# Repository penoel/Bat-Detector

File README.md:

# Bat-Detector
The bat detector takes ultrasonic sound from a source (bat, transmitter, etc) and adds it to a local oscillator.  The combined signal has a beat frequency (intermediate frequency) that is then filter to remove the higher frequencies.  It is currently used with a transmitter to show doppler shift.  The transmitter is mounted on a pendulum that swings towards and away from the detector.
## R7 should be 1.5k&#937; not ~~47k&#937;~~, R9 should be 560 &#937; not ~~1k&#937;~~, and lastly R11 should be 1k&#937; not ~~4.7k&#937;~~
These values work a lot better with this op amp (other values were better for the first one I used)

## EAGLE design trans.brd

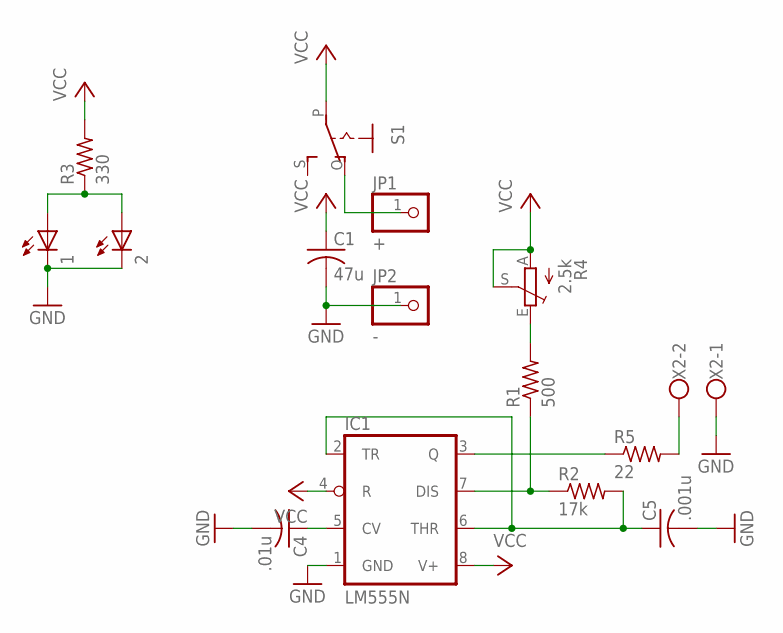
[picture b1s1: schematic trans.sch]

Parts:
1, 2: LED3MM
C1: 47u; C050-025X075
C4: .01u; C025-025X050
C5: .001u; C025-025X050
IC1: LM555N; DIL08
JP1: +; 1X01
JP2: -; 1X01
R1: 500; 0207/10
R2: 17k; 0207/10
R3: 330; 0207/10
R4: 2.5k; CA9V
R5: 22; 0207/10
S1: EG1218S; EG1218
X2: W237-102

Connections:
GND: 1.K (C), 2.K (C), C1.2, C4.2, C5.2, IC1.1 (GND), JP2.1, X2.1
unnamed: 1.A, 2.A, R3.1
unnamed: C4.1, IC1.5 (CV)
unnamed: C5.1, IC1.2 (TR), IC1.6 (THR), R2.2
unnamed: IC1.7 (DIS), R1.1, R2.1
unnamed: R1.2, R4.E
unnamed: IC1.3 (Q), R5.1
unnamed: JP1.1, S1.O
unnamed: R5.2, X2.2
VCC: C1.1, IC1.4 (R), IC1.8 (V+), R3.2, R4.A, R4.S, S1.P

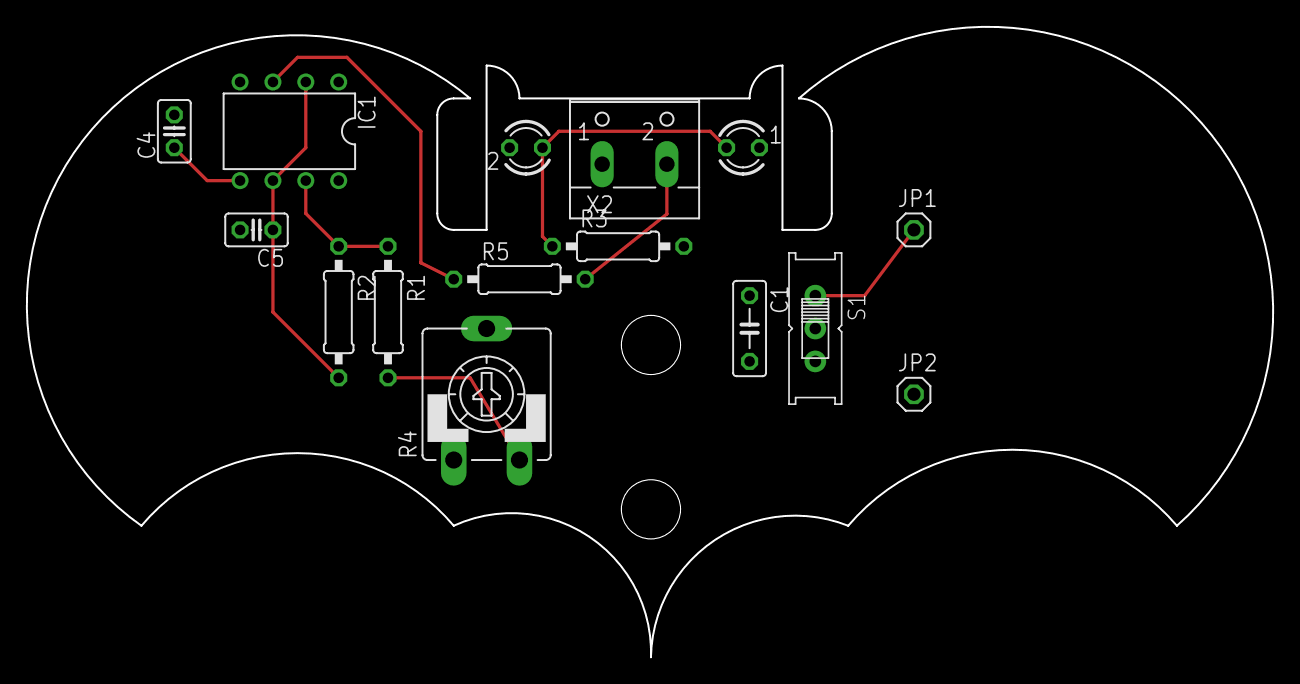
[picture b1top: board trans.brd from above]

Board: 2 copper layers, 96.3 x 48.7 mm, 15 parts (0 on the bottom side), 10 nets.

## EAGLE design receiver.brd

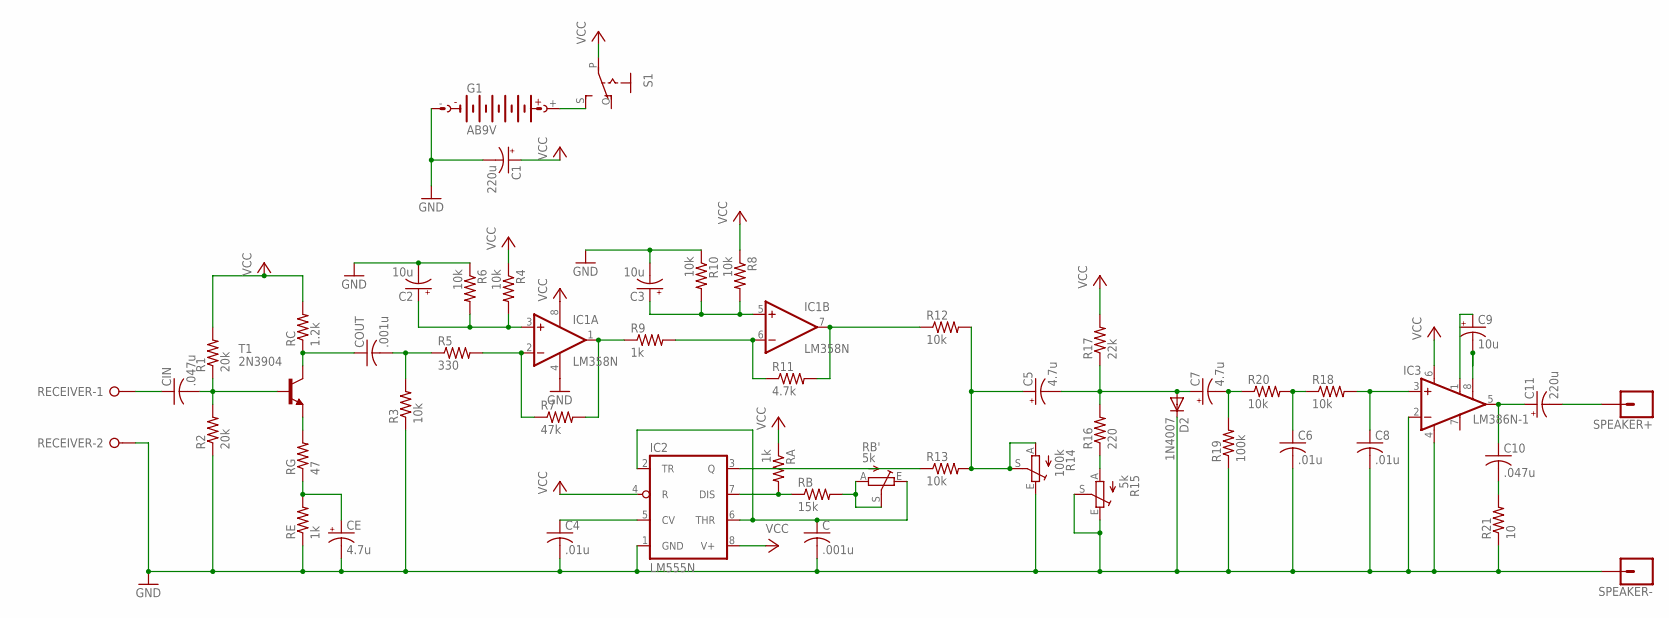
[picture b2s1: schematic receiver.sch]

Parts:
C: .001u; C050-024X044
C1, C11: 220u; B45181B
C2, C3, C9: 10u; B45181B
C4, C6, C8: .01u; C050-024X044
C5, C7: 4.7u; B45181B
C10: .047u; C050-024X044
CE: 4.7u; B45181B
CIN: .047u; C050-024X044
COUT: .001u; C050-024X044
D2: 1N4007; DO41-10
G1: AB9V
IC1: LM358N; DIL08
IC2: LM555N; DIL08-ROUND
IC3: LM386N-1; DIL08
R1, R2: 20k; 0207/10
R3, R4, R6, R8, R10, R12, R13, R18, R20: 10k; 0207/10
R5: 330; 0207/10
R7: 47k; 0207/10
R9: 1k; 0207/10
R11: 4.7k; 0207/10
R14: 100k; B25P
R15: 5k; B25P
R16: 220; 0207/10
R17: 22k; 0207/10
R19: 100k; 0207/10
R21: 10; 0207/10
RA: 1k; 0207/10
RB: 15k; 0207/10
RB': 5k; B25P
RC: 1.2k; 0207/10
RE: 1k; 0207/10
RECEIVER: W237-02P; W237-132
RG: 47; 0207/10
S1: EG1218S; EG1218
SPEAKER+: CONN_01; 1X01
SPEAKER-: CONN_01; 1X01
T1: 2N3904; TO92

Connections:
GND: C.2, C1.-, C2.-, C3.-, C4.2, C6.2, C8.2, CE.-, D2.C, G1.-, IC1.4 (V-), IC2.1 (GND), IC3.2 (-IN), IC3.4 (GND), R2.1, R3.1, R6.1, R10.1, R14.E, R15.E, R15.S, R19.1, R21.1, RE.1, RECEIVER.2, SPEAKER-.1
unnamed: CIN.1, RECEIVER.1
unnamed: CIN.2, R1.1, R2.2, T1.2 (B)
unnamed: COUT.2, R3.2, R5.1
unnamed: COUT.1, RC.1, T1.1 (C)
unnamed: RG.2, T1.3 (E)
unnamed: CE.+, RE.2, RG.1
unnamed: IC1.2 (-IN), R5.2, R7.1
unnamed: C2.+, IC1.3 (+IN), R4.2, R6.2
unnamed: C4.1, IC2.5 (CV)
unnamed: IC1.1 (OUT), R7.2, R9.1
unnamed: IC1.6 (-IN), R9.2, R11.1
unnamed: C.1, IC2.2 (TR), IC2.6 (THR), RB'.E
unnamed: IC1.7 (OUT), R11.2, R12.1
unnamed: C3.+, IC1.5 (+IN), R8.2, R10.2
unnamed: IC2.7 (DIS), RA.2, RB.1
unnamed: RB.2, RB'.A, RB'.S
unnamed: IC2.3 (Q), R13.1
unnamed: C5.+, R12.2, R13.2, R14.A, R14.S
unnamed: R15.A, R16.1
unnamed: C5.-, C7.+, D2.A, R16.2, R17.1
unnamed: C11.-, SPEAKER+.1
unnamed: C7.-, R19.2, R20.1
unnamed: C6.1, R18.1, R20.2
unnamed: C8.1, IC3.3 (+IN), R18.2
unnamed: C9.-, IC3.8 (GAIN)
unnamed: C9.+, IC3.1 (GAIN)
unnamed: C10.1, C11.+, IC3.5 (OUT)
unnamed: C10.2, R21.2
unnamed: G1.+, S1.S
VCC: C1.+, IC1.8 (V+), IC2.4 (R), IC2.8 (V+), IC3.6 (VS), R1.2, R4.1, R8.1, R17.2, RA.1, RC.2, S1.P

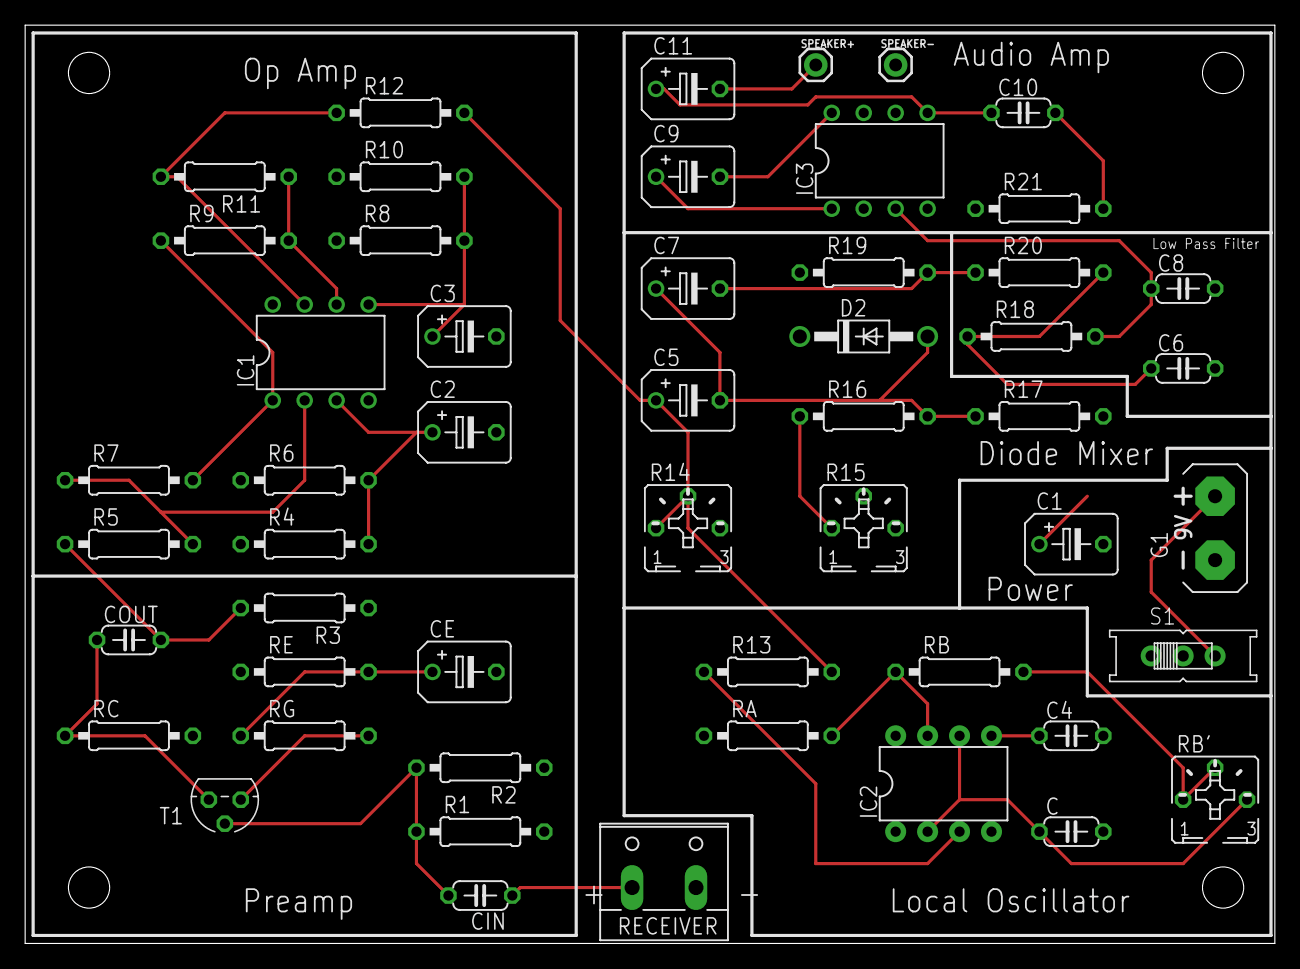
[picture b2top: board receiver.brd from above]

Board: 2 copper layers, 99.4 x 73.0 mm, 52 parts (0 on the bottom side), 31 nets.

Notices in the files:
parts and their libraries:
SparkFun-Connectors: Licensing: Creative Commons ShareAlike 4.0 International - https://creativecommons.org/licenses/by-sa/4.0
